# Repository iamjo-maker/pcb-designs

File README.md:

# pcb-designs
This repository contains PCB designs developed as part of coursework and independent exploration in hardware design.

## Tools Used
- Your software: KiCad

## Files included (for each project)
- Schematics
- PCB layout files
- Exported renders (if available)

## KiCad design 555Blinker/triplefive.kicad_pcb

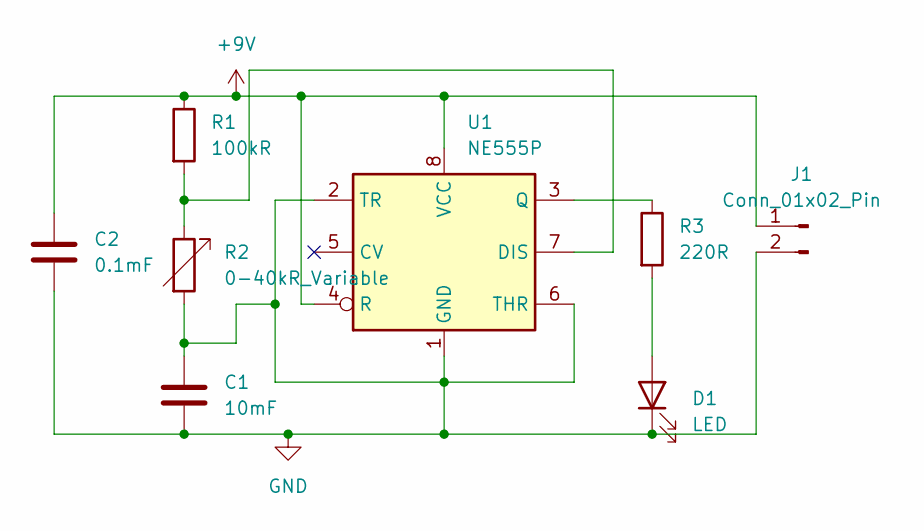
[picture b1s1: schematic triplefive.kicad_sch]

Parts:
C1: 10mF; CP_Radial_D4.0mm_P2.00mm
C2: 0.1mF; CP_Radial_D4.0mm_P2.00mm
D1: LED; LED_D3.0mm
J1: Conn_01x02_Pin; JWT_A3963_1x02_P3.96mm_Vertical
R1: 100kR; R_Axial_DIN0207_L6.3mm_D2.5mm_P7.62mm_Horizontal
R2: 0-40kR_Variable; Potentiometer_Piher_PT-6-V_Vertical
R3: 220R; R_Axial_DIN0207_L6.3mm_D2.5mm_P7.62mm_Horizontal
U1: NE555P; DIP-8_W7.62mm

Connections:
+9V: C2.1, J1.1, R1.1, U1.4 (R), U1.8 (VCC)
GND: C1.1, C1.2, C2.2, D1.1 (K), J1.2, R2.2, U1.1 (GND), U1.2 (TR), U1.6 (THR)
unnamed: D1.2 (A), R3.2
unnamed: R1.2, R2.1, U1.7 (DIS)
unnamed: R3.1, U1.3 (Q)

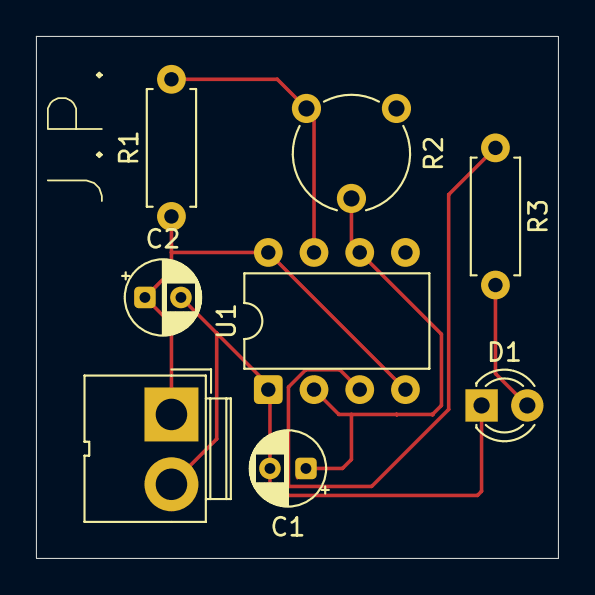
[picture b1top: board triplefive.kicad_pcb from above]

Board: 2 copper layers, 29.0 x 29.0 mm, 8 parts (0 on the bottom side), 5 nets.

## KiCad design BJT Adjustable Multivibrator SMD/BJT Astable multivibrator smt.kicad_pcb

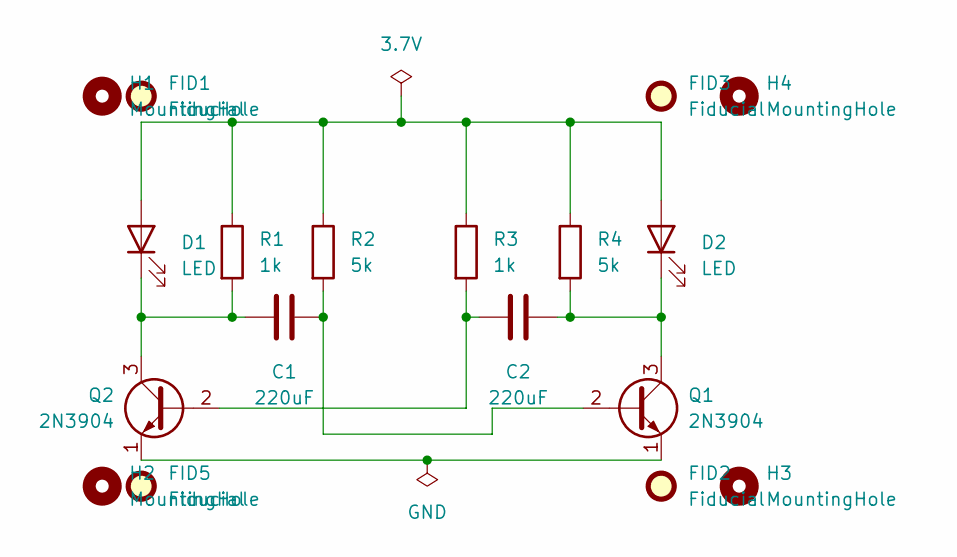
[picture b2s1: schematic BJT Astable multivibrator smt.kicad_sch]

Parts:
C1, C2: 220uF; C_0805_2012Metric_Pad1.18x1.45mm_HandSolder
D1, D2: LED; LED_0805_2012Metric_Pad1.15x1.40mm_HandSolder
FID1, FID2, FID3, FID5: Fiducial; Fiducial_0.5mm_Mask1.5mm
H1, H2, H3, H4: MountingHole; MountingHole_2.1mm
Q1, Q2: 2N3904; TO-92_Inline
R1, R3: 1k; R_0805_2012Metric_Pad1.20x1.40mm_HandSolder
R2, R4: 5k; R_0805_2012Metric_Pad1.20x1.40mm_HandSolder

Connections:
unnamed: D1.2 (A), D2.2 (A), R1.1, R2.1, R3.1, R4.1
unnamed: C1.1, D1.1 (K), Q2.3 (C), R1.2
unnamed: C2.2, D2.1 (K), Q1.3 (C), R4.2
unnamed: C1.2, Q1.2 (B), R2.2
unnamed: Q1.1 (E), Q2.1 (E)
unnamed: C2.1, Q2.2 (B), R3.2

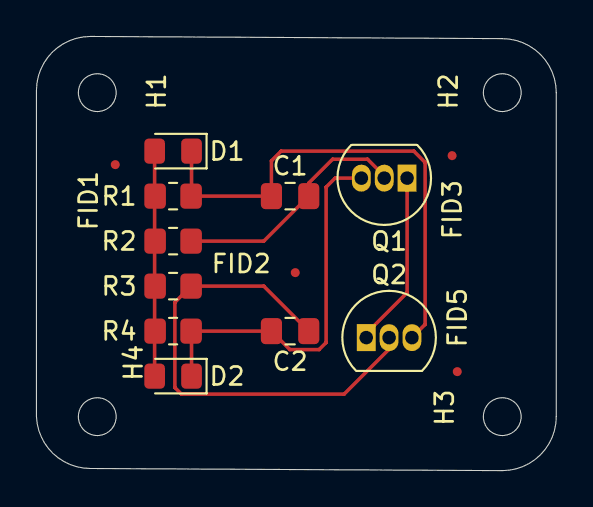
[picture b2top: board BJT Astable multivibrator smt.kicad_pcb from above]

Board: 2 copper layers, 28.9 x 24.1 mm, 18 parts (0 on the bottom side), 6 nets.

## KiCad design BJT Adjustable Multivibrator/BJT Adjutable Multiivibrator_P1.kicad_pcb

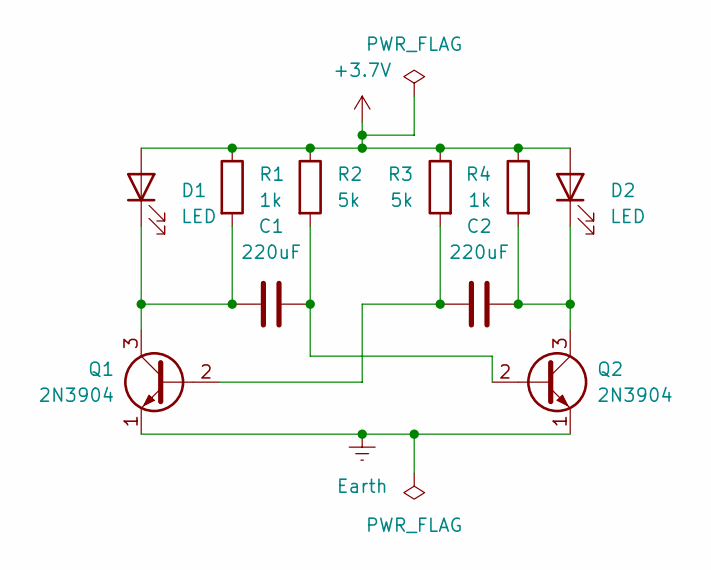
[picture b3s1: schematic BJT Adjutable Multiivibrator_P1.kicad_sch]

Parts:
C1, C2: 220uF; C_Radial_D4.0mm_H7.0mm_P1.50mm
D1, D2: LED; LED_D1.8mm_W3.3mm_H2.4mm
Q1, Q2: 2N3904; TO-92_Inline
R1, R4: 1k; R_Axial_DIN0207_L6.3mm_D2.5mm_P7.62mm_Horizontal
R2, R3: 5k; R_Axial_DIN0207_L6.3mm_D2.5mm_P7.62mm_Horizontal

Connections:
+3.7V: D1.2 (A), D2.2 (A), R1.1, R2.1, R3.1, R4.1
Earth: Q1.1 (E), Q2.1 (E)
unnamed: C1.1, D1.1 (K), Q1.3 (C), R1.2
unnamed: C2.2, D2.1 (K), Q2.3 (C), R4.2
unnamed: C2.1, Q1.2 (B), R3.2
unnamed: C1.2, Q2.2 (B), R2.2

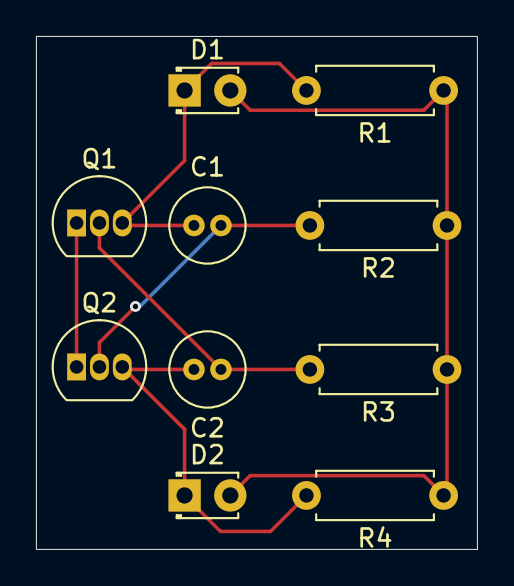
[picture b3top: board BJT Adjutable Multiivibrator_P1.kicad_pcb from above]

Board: 2 copper layers, 24.5 x 28.5 mm, 10 parts (0 on the bottom side), 6 nets.

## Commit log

2026-05-03 update README
    Added tools used and project files sections to README.
